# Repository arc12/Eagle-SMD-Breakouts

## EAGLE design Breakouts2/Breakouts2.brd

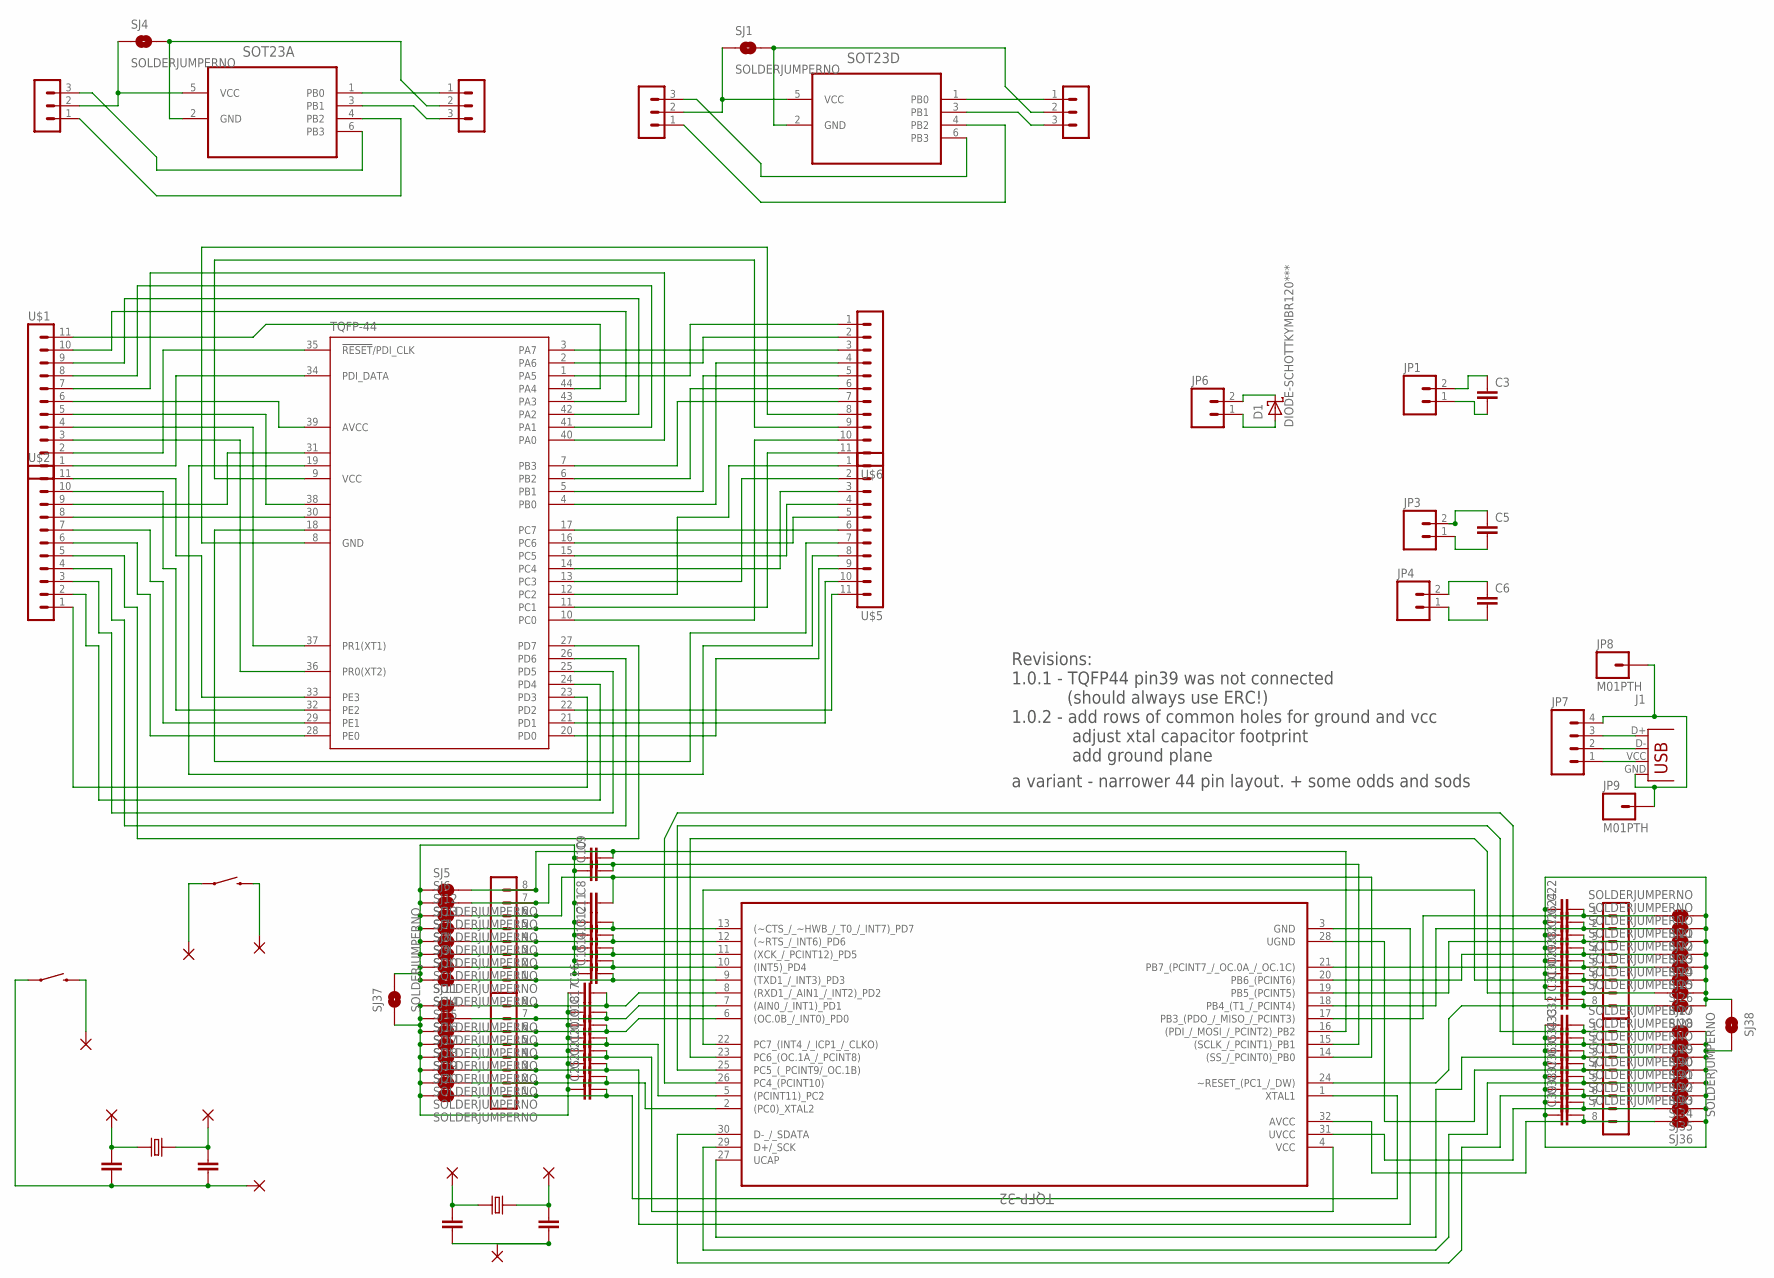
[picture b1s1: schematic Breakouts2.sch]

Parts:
C1, C2, C40, C41: C-EU025-024X044**100NF+22PF; C025-024X044
C3, C5, C6, C8, C9, C10, C11, C12, C13, C14, C15, C16, C17, C18, C19, C20, C21, C22, C23, C24, C25, C26, C27, C28, C29, C30, C31, C32, C33, C34, C35, C36, C37, C38, C39: C-EU1206; 1206
D1: DIODE-SCHOTTKYMBR120***; SOD123
J1: USB-FCI_SMD***; FCI_USB_B_SMD
JP1, JP3, JP4, JP6: M02PTH; 1X02
JP7: M04PTH; 1X04
JP8, JP9: M01PTH; 1X01
PAD1, PAD2, PAD3, PAD4, PAD5, PAD6, PAD7, PAD8, PAD9: WIREPAD1,6/0,8; 1,6/0,8
S1, S2: SWITCH-MOMENTARY-2PTH; TACTILE-PTH
SJ1, SJ4, SJ5, SJ6, SJ7, SJ8, SJ9, SJ10, SJ11, SJ12, SJ13, SJ14, SJ15, SJ16, SJ17, SJ18, SJ19, SJ20, SJ21, SJ22, SJ23, SJ24, SJ25, SJ26, SJ27, SJ28, SJ29, SJ30, SJ31, SJ32, SJ33, SJ34, SJ35, SJ36, SJ37, SJ38: SOLDERJUMPERNO; SJ_2S-NO
SOT23A, SOT23D: ATTINY10-TSHR; SOT95P280X145-6N
SV4, SV8, SV16, SV18: MA08-1
SV12, SV13, SV14, SV15: MA03-1
TQFP-32: AT90USB162-16AU; QFP80P900X900X120-32N
TQFP-44: XMEGA16A4A; TQFP44
U$1, U$2, U$5, U$6: MA11-1; MA11-1S
X1, X2: CRYSTAL-HC49U-V**16MHZ; HC49U-V

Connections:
GND: C1.2, C2.2, PAD8.1, S1.1
GND1: PAD4.1, S2.1
unnamed: TQFP-44.1 (PA5), U$6.1
unnamed: TQFP-44.2 (PA6), U$6.2
unnamed: TQFP-44.3 (PA7), U$6.3
unnamed: TQFP-44.4 (PB0), U$6.4
unnamed: TQFP-44.5 (PB1), U$6.5
unnamed: TQFP-44.6 (PB2), U$6.6
unnamed: TQFP-44.7 (PB3), U$6.7
unnamed: TQFP-44.8 (GND), U$6.8
unnamed: TQFP-44.9 (VCC), U$6.9
unnamed: TQFP-44.12 (PC2), U$5.1
unnamed: TQFP-44.11 (PC1), U$6.11
unnamed: TQFP-44.10 (PC0), U$6.10
unnamed: TQFP-44.13 (PC3), U$5.2
unnamed: TQFP-44.14 (PC4), U$5.3
unnamed: TQFP-44.15 (PC5), U$5.4
unnamed: TQFP-44.16 (PC6), U$5.5
unnamed: TQFP-44.17 (PC7), U$5.6
unnamed: TQFP-44.18 (GND1), U$5.7
unnamed: TQFP-44.19 (VCC1), U$5.8
unnamed: TQFP-44.20 (PD0), U$5.9
unnamed: TQFP-44.21 (PD1), U$5.10
unnamed: TQFP-44.22 (PD2), U$5.11
unnamed: TQFP-44.23 (PD3), U$2.1
unnamed: TQFP-44.24 (PD4), U$2.2
unnamed: C8.1, C9.1, C10.1, C11.1, C12.1, C13.1, C14.1, C15.1, SJ5.1, SJ6.1, SJ7.1, SJ8.1, SJ9.1, SJ10.1, SJ12.1, SJ13.1, SJ37.2
unnamed: C24.2, SJ22.2, SV4.2, TQFP-32.18 (PB4_(T1_/_PCINT4))
unnamed: C22.1, C24.1, C26.1, C27.1, C28.1, C29.1, C30.1, C31.1, SJ21.1, SJ22.1, SJ23.1, SJ24.1, SJ25.1, SJ26.1, SJ27.1, SJ28.1, SJ38.1
unnamed: C32.1, C33.1, C34.1, C35.1, C36.1, C37.1, C38.1, C39.1, SJ29.1, SJ30.1, SJ31.1, SJ32.1, SJ33.1, SJ34.1, SJ35.1, SJ36.1, SJ38.2
unnamed: C26.2, SJ23.2, SV4.3, TQFP-32.19 (PB5_(PCINT5))
unnamed: C16.1, C17.1, C18.1, C19.1, C20.1, C21.1, C23.1, C25.1, SJ11.1, SJ14.1, SJ15.1, SJ16.1, SJ17.1, SJ18.1, SJ19.1, SJ20.1, SJ37.1
unnamed: C27.2, SJ24.2, SV4.4, TQFP-32.20 (PB6_(PCINT6))
unnamed: J1.GND, JP7.4, JP8.1, JP9.1
unnamed: TQFP-44.25 (PD5), U$2.3
unnamed: TQFP-44.26 (PD6), U$2.4
unnamed: TQFP-44.27 (PD7), U$2.5
unnamed: TQFP-44.28 (PE0), U$2.6
unnamed: TQFP-44.29 (PE1), U$2.7
unnamed: TQFP-44.30 (GND2), U$2.8
unnamed: TQFP-44.31 (VCC2), U$2.9
unnamed: TQFP-44.32 (PE2), U$2.10
unnamed: TQFP-44.33 (PE3), U$2.11
unnamed: TQFP-44.34 (PDI_DATA), U$1.1
unnamed: TQFP-44.35 (!RESET!/PDI_CLK), U$1.2
unnamed: TQFP-44.36 (PR0(XT2)), U$1.3
unnamed: TQFP-44.37 (PR1(XT1)), U$1.4
unnamed: C41.1, PAD2.1, X2.1
unnamed: C40.1, PAD5.1, X2.2
unnamed: J1.D+, JP7.3
unnamed: J1.D-, JP7.2
unnamed: J1.VCC (VBUS), JP7.1
unnamed: PAD3.1, S2.3 (2)
unnamed: C3.1, JP1.2
unnamed: C3.2, JP1.1
unnamed: C5.1, JP3.2
unnamed: C5.2, JP3.1
unnamed: D1.K (C), JP6.2
unnamed: D1.A, JP6.1
unnamed: C6.1, JP4.2
unnamed: C6.2, JP4.1
unnamed: TQFP-44.38 (GND3), U$1.5
unnamed: TQFP-44.39 (AVCC), U$1.6
unnamed: TQFP-44.40 (PA0), U$1.7
unnamed: TQFP-44.41 (PA1), U$1.8
unnamed: TQFP-44.42 (PA2), U$1.9
unnamed: TQFP-44.43 (PA3), U$1.10
unnamed: TQFP-44.44 (PA4), U$1.11
unnamed: C23.2, SJ19.2, SV16.2, TQFP-32.2 ((PC0)_XTAL2)
unnamed: C25.2, SJ20.2, SV16.1, TQFP-32.1 (XTAL1)
unnamed: C19.2, SJ16.2, SV16.5, TQFP-32.5 ((PCINT11)_PC2)
unnamed: C18.2, SJ15.2, SV16.6, TQFP-32.6 ((OC.0B_/_INT0)_PD0)
unnamed: C17.2, SJ14.2, SV16.7, TQFP-32.7 ((AIN0_/_INT1)_PD1)
unnamed: C16.2, SJ11.2, SV16.8, TQFP-32.8 ((RXD1_/_AIN1_/_INT2)_PD2)
unnamed: C15.2, SJ10.2, SV18.1, TQFP-32.9 ((TXD1_/_INT3)_PD3)
unnamed: C14.2, SJ9.2, SV18.2, TQFP-32.10 ((INT5)_PD4)
unnamed: C13.2, SJ8.2, SV18.3, TQFP-32.11 ((XCK_/_PCINT12)_PD5)
unnamed: C12.2, SJ7.2, SV18.4, TQFP-32.12 ((~RTS_/_INT6)_PD6)
unnamed: C11.2, SJ13.2, SV18.5, TQFP-32.13 ((~CTS_/_~HWB_/_T0_/_INT7)_PD7)
unnamed: C20.2, SJ17.2, SV16.4, TQFP-32.4 (VCC)
unnamed: C21.2, SJ18.2, SV16.3, TQFP-32.3 (GND)
unnamed: C9.2, SJ5.2, SV18.8, TQFP-32.16 ((PDI_/_MOSI_/_PCINT2)_PB2)
unnamed: C10.2, SJ6.2, SV18.7, TQFP-32.15 ((SCLK_/_PCINT1)_PB1)
unnamed: C8.2, SJ12.2, SV18.6, TQFP-32.14 ((SS_/_PCINT0)_PB0)
unnamed: C22.2, SJ21.2, SV4.1, TQFP-32.17 (PB3_(PDO_/_MISO_/_PCINT3))
unnamed: C28.2, SJ25.2, SV4.5, TQFP-32.21 (PB7_(PCINT7_/_OC.0A_/_OC.1C))
unnamed: C29.2, SJ26.2, SV4.6, TQFP-32.22 (PC7_(INT4_/_ICP1_/_CLKO))
unnamed: C30.2, SJ27.2, SV4.7, TQFP-32.23 (PC6_(OC.1A_/_PCINT8))
unnamed: C31.2, SJ28.2, SV4.8, TQFP-32.24 (~RESET_(PC1_/_DW))
unnamed: C32.2, SJ29.2, SV8.1, TQFP-32.25 (PC5_(_PCINT9/_OC.1B))
unnamed: C33.2, SJ30.2, SV8.2, TQFP-32.26 (PC4_(PCINT10))
unnamed: C34.2, SJ31.2, SV8.3, TQFP-32.27 (UCAP)
unnamed: C35.2, SJ32.2, SV8.4, TQFP-32.28 (UGND)
unnamed: C36.2, SJ33.2, SV8.5, TQFP-32.29 (D+/_SCK)
unnamed: C37.2, SJ34.2, SV8.6, TQFP-32.30 (D-_/_SDATA)
unnamed: C38.2, SJ35.2, SV8.7, TQFP-32.31 (UVCC)
unnamed: C39.2, SJ36.2, SV8.8, TQFP-32.32 (AVCC)
unnamed: SOT23D.1 (PB0), SV13.1
unnamed: SJ1.2, SOT23D.2 (GND), SV13.2
unnamed: SOT23D.3 (PB1), SV13.3
unnamed: SOT23D.4 (PB2), SV12.1
unnamed: SJ1.1, SOT23D.5 (VCC), SV12.2
unnamed: SOT23D.6 (PB3), SV12.3
unnamed: SOT23A.1 (PB0), SV15.1
unnamed: SJ4.2, SOT23A.2 (GND), SV15.2
unnamed: SOT23A.3 (PB1), SV15.3
unnamed: SOT23A.4 (PB2), SV14.1
unnamed: SJ4.1, SOT23A.5 (VCC), SV14.2
unnamed: SOT23A.6 (PB3), SV14.3
unnamed: PAD1.1, S1.3 (2)
unnamed: C2.1, PAD6.1, X1.1
unnamed: C1.1, PAD7.1, X1.2
XTAL_GND: C40.2, C41.2, PAD9.1

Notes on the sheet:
Revisions: 1.0.1 - TQFP44 pin39 was not connected (should always use ERC!) 1.0.2 - add rows of common holes for ground and vcc adjust xtal capacitor footprint add ground plane
a variant - narrower 44 pin layout. + some odds and sods

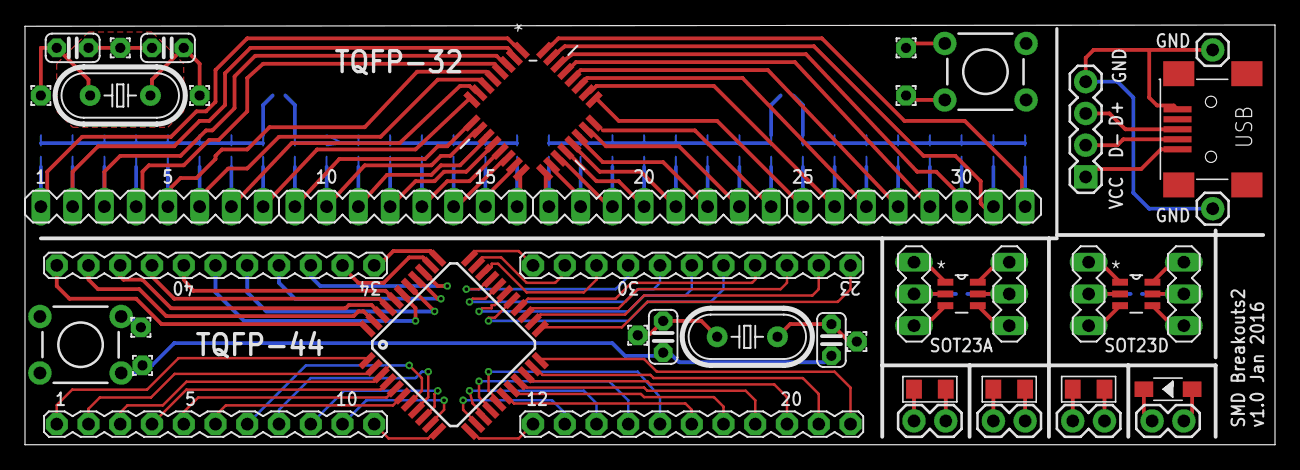
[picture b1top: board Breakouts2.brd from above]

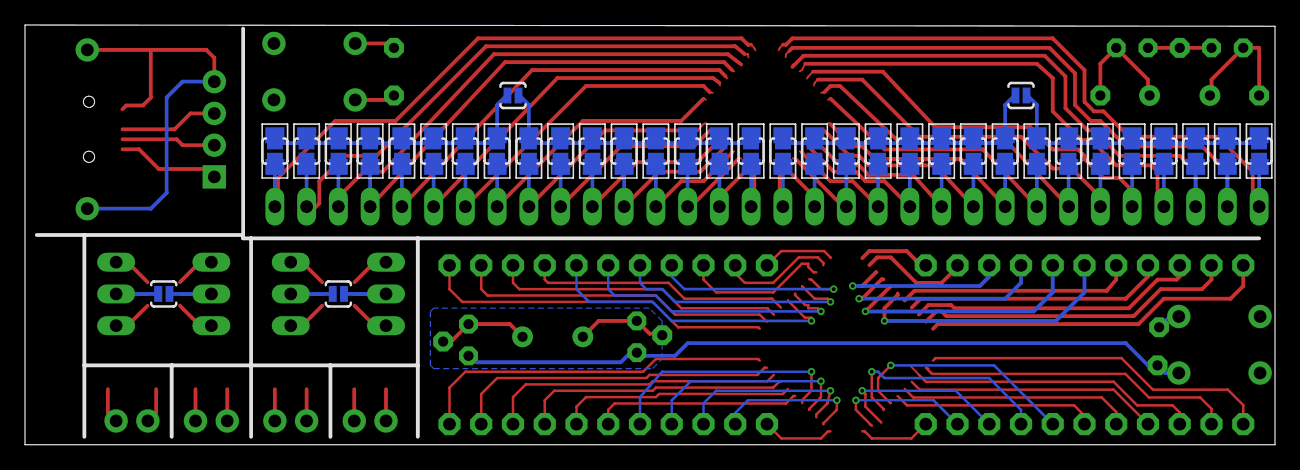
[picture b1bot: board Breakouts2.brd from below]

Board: 2 copper layers, 100.0 x 33.6 mm, 113 parts (68 on the bottom side), 113 nets.

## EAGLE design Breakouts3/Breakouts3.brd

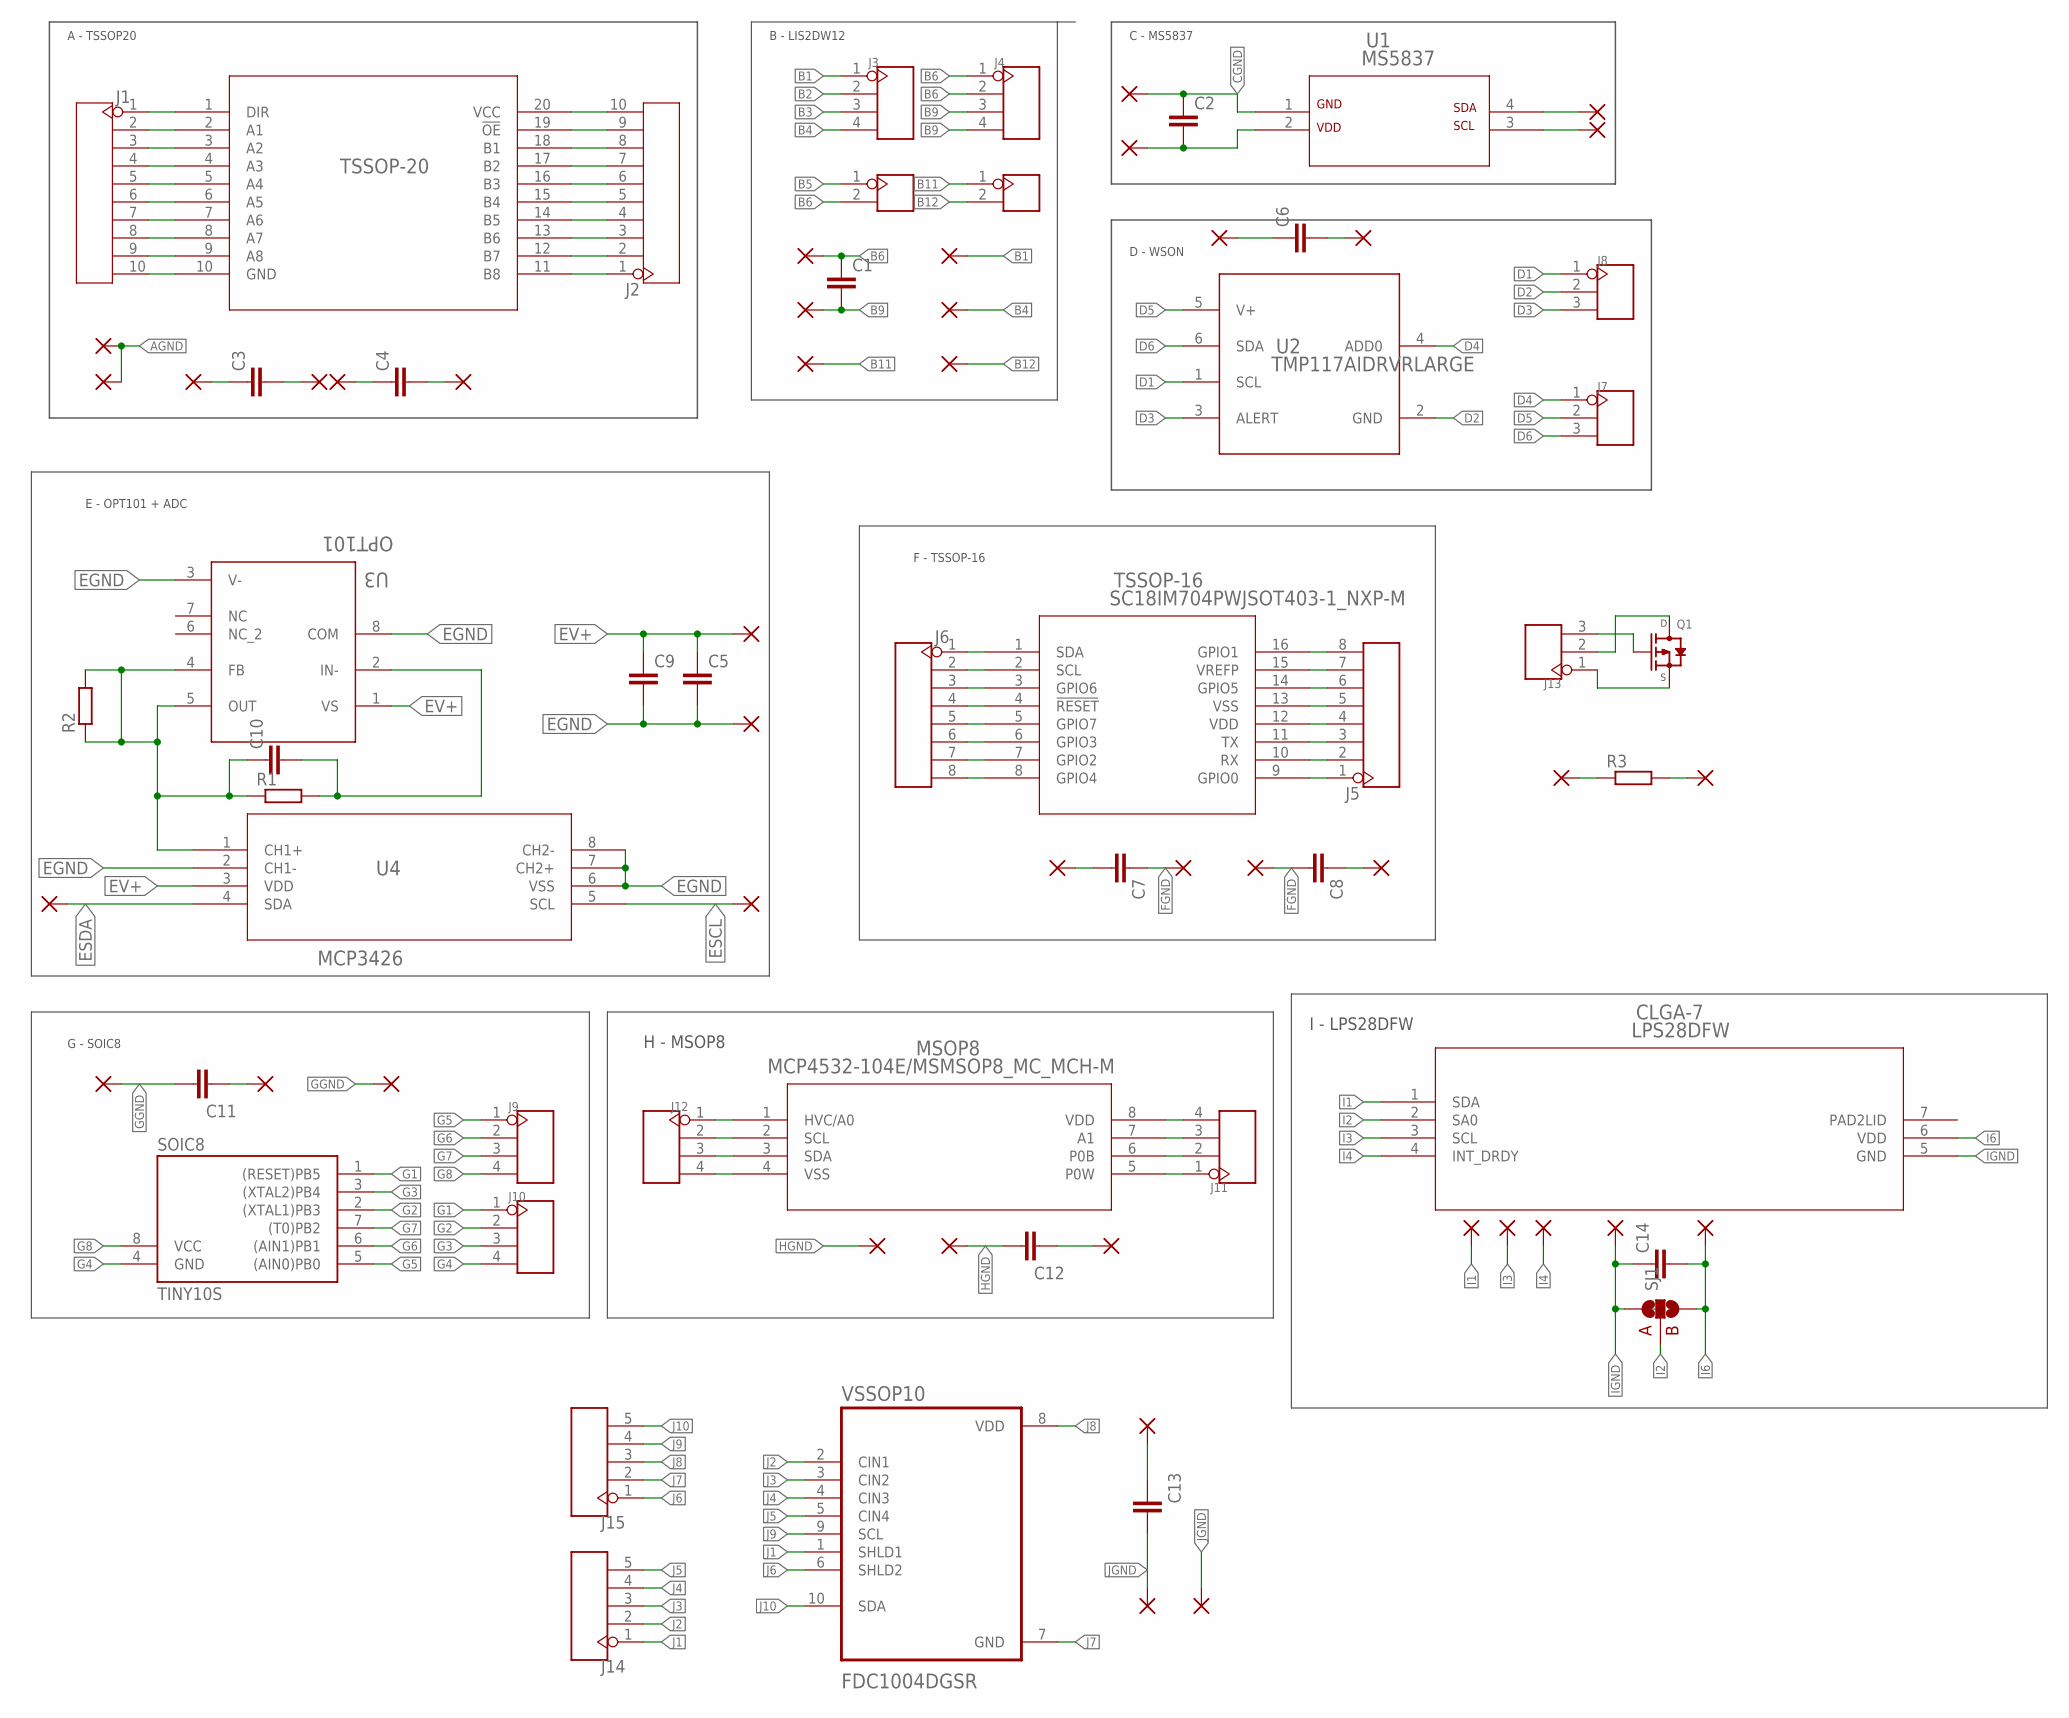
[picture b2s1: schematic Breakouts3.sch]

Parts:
C1, C2, C3, C4, C5, C6, C7, C8, C9, C10, C11, C12, C13, C14: C-EU1206; 1206
CLGA-7: LPS28DFW; CCLGA7_LPS28DFW_LARGE
J1, J2: HEADER-10P-2.54; 10P-2.54
J3, J4: HEADER-4P-SMD-1.27; 4P-1.27-SMD
J5, J6: HEADER-8P-2.54; 8P-2.54
J7, J8, J13: HEADER-3P-2.54; 3P-2.54
J9, J10, J11, J12: HEADER-4P-60/35MIL; 4P-65/35MIL
J14, J15: HEADER-5P-2.54; 5P-2.54
MSOP8: MCP4532-104E/MSMSOP8_MC_MCH-M; MSOP8_MC_MCH-M
PAD1, PAD2, PAD3, PAD4, PAD5, PAD6, PAD7, PAD8, PAD9, PAD10, PAD11, PAD12, PAD13, PAD14, PAD15, PAD16, PAD17, PAD18, PAD19, PAD20, PAD21, PAD22, PAD23, PAD24, PAD25, PAD26, PAD27, PAD28, PAD29, PAD30, PAD31, PAD32, PAD33, PAD34, PAD35, PAD36, PAD37, PAD38, PAD39, PAD40, PAD41, PAD42: WIREPADSMD1,27-254; SMD1,27-2,54
Q1: FDN338P_PMOSSOT23_LONG; SOT23_LONG
R1, R2, R3: R-EU_; 1206
SJ1: SOLDERJUMPER_2WAYT; SJ_2
SOIC8: TINY10S; SOIC8
TSSOP-16: SC18IM704PWJSOT403-1_NXP-M; SOT403-1_NXP-M
TSSOP-20: SN74ACT245PWRPW20-M; PW20-M
U1: MS5837; MS5837-02BA01_LARGE
U2: TMP117AIDRVRLARGE; DRV0006B-LARGE
U3: OPT101; DTL0008A_LARGE
U4: MCP3426; SOIC8-N_MC_MCH
U$1, U$2: HEADER-2P; 2P-1.27-SMD
VSSOP10: FDC1004DGSR; SOP50P490X110-10N

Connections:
AGND: PAD15.1, PAD16.1
B1: J3.1, PAD3.1
B2: J3.2
B3: J3.3
B4: J3.4, PAD6.1
B5: U$1.1
B6: C1.1, J4.1, J4.2, PAD1.1, U$1.2
B9: C1.2, J4.3, J4.4, PAD2.1
B11: PAD4.1, U$2.1
B12: PAD5.1, U$2.2
CGND: C2.1, PAD7.1, U1.1 (GND)
D1: J8.1, U2.1 (SCL)
D2: J8.2, U2.2 (GND)
D3: J8.3, U2.3 (ALERT)
D4: J7.1, U2.4 (ADD0)
D5: J7.2, U2.5 (V+)
D6: J7.3, U2.6 (SDA)
EGND: C5.2, C9.2, PAD24.1, U3.3 (V-), U3.8 (COM), U4.2 (CH1-), U4.6 (VSS), U4.7 (CH2+), U4.8 (CH2-)
ESCL: PAD25.1, U4.5 (SCL)
ESDA: PAD26.1, U4.4 (SDA)
EV+: C5.1, C9.1, PAD23.1, U3.1 (VS), U4.3 (VDD)
FGND: C7.1, C8.2, PAD20.1, PAD21.1
G1: J10.1, SOIC8.1 ((RESET)PB5)
G2: J10.2, SOIC8.2 ((XTAL1)PB3)
G3: J10.3, SOIC8.3 ((XTAL2)PB4)
G4: J10.4, SOIC8.4 (GND)
G5: J9.1, SOIC8.5 ((AIN0)PB0)
G6: J9.2, SOIC8.6 ((AIN1)PB1)
G7: J9.3, SOIC8.7 ((T0)PB2)
G8: J9.4, SOIC8.8 (VCC)
GGND: C11.1, PAD27.1, PAD29.1
HGND: C12.1, PAD31.1, PAD32.1
I1: CLGA-7.1 (SDA), PAD34.1
I2: CLGA-7.2 (SA0), SJ1.2
I3: CLGA-7.3 (SCL), PAD35.1
I4: CLGA-7.4 (INT_DRDY), PAD36.1
I6: C14.2, CLGA-7.6 (VDD), PAD38.1, SJ1.3
IGND: C14.1, CLGA-7.5 (GND), PAD37.1, SJ1.1
J1: J14.1, VSSOP10.1 (SHLD1)
J2: J14.2, VSSOP10.2 (CIN1)
J3: J14.3, VSSOP10.3 (CIN2)
J4: J14.4, VSSOP10.4 (CIN3)
J5: J14.5, VSSOP10.5 (CIN4)
J6: J15.1, VSSOP10.6 (SHLD2)
J7: J15.2, VSSOP10.7 (GND)
J8: J15.3, VSSOP10.8 (VDD)
J9: J15.4, VSSOP10.9 (SCL)
J10: J15.5, VSSOP10.10 (SDA)
JGND: C13.1, PAD41.1, PAD42.1
unnamed: J1.1, TSSOP-20.1 (DIR)
unnamed: C2.2, PAD8.1, U1.2 (VDD)
unnamed: PAD9.1, U1.4 (SDA)
unnamed: PAD10.1, U1.3 (SCL)
unnamed: J1.2, TSSOP-20.2 (A1)
unnamed: J1.3, TSSOP-20.3 (A2)
unnamed: J1.4, TSSOP-20.4 (A3)
unnamed: J1.5, TSSOP-20.5 (A4)
unnamed: J1.6, TSSOP-20.6 (A5)
unnamed: J1.7, TSSOP-20.7 (A6)
unnamed: J1.8, TSSOP-20.8 (A7)
unnamed: J1.9, TSSOP-20.9 (A8)
unnamed: J1.10, TSSOP-20.10 (GND)
unnamed: J2.10, TSSOP-20.20 (VCC)
unnamed: J2.9, TSSOP-20.19 (!OE)
unnamed: J2.8, TSSOP-20.18 (B1)
unnamed: J2.7, TSSOP-20.17 (B2)
unnamed: J2.6, TSSOP-20.16 (B3)
unnamed: J2.5, TSSOP-20.15 (B4)
unnamed: J2.4, TSSOP-20.14 (B5)
unnamed: J2.3, TSSOP-20.13 (B6)
unnamed: J2.2, TSSOP-20.12 (B7)
unnamed: J2.1, TSSOP-20.11 (B8)
unnamed: C3.1, PAD11.1
unnamed: C3.2, PAD13.1
unnamed: C4.1, PAD12.1
unnamed: C4.2, PAD14.1
unnamed: C6.1, PAD17.1
unnamed: C6.2, PAD18.1
unnamed: C7.2, PAD22.1
unnamed: PAD33.1, R3.1
unnamed: C10.1, R1.1, R2.1, R2.2, U3.4 (FB), U3.5 (OUT), U4.1 (CH1+)
unnamed: C8.1, PAD19.1
unnamed: J6.1, TSSOP-16.1 (SDA)
unnamed: J6.2, TSSOP-16.2 (SCL)
unnamed: J6.3, TSSOP-16.3 (GPIO6)
unnamed: J6.4, TSSOP-16.4 (!RESET)
unnamed: J6.5, TSSOP-16.5 (GPIO7)
unnamed: J6.6, TSSOP-16.6 (GPIO3)
unnamed: J6.7, TSSOP-16.7 (GPIO2)
unnamed: J6.8, TSSOP-16.8 (GPIO4)
unnamed: J5.8, TSSOP-16.16 (GPIO1)
unnamed: J5.7, TSSOP-16.15 (VREFP)
unnamed: J5.6, TSSOP-16.14 (GPIO5)
unnamed: J5.5, TSSOP-16.13 (VSS)
unnamed: J5.4, TSSOP-16.12 (VDD)
unnamed: J5.3, TSSOP-16.11 (TX)
unnamed: J5.2, TSSOP-16.10 (RX)
unnamed: J5.1, TSSOP-16.9 (GPIO0)
unnamed: C10.2, R1.2, U3.2 (IN-)
unnamed: C11.2, PAD28.1
unnamed: J12.1, MSOP8.1 (HVC/A0)
unnamed: J12.2, MSOP8.2 (SCL)
unnamed: J12.3, MSOP8.3 (SDA)
unnamed: J12.4, MSOP8.4 (VSS)
unnamed: J11.4, MSOP8.8 (VDD)
unnamed: J11.3, MSOP8.7 (A1)
unnamed: J11.2, MSOP8.6 (P0B)
unnamed: J11.1, MSOP8.5 (P0W)
unnamed: PAD39.1, R3.2
unnamed: C12.2, PAD30.1
unnamed: J13.3, Q1.1 (G)
unnamed: J13.2, Q1.3 (D)
unnamed: J13.1, Q1.2 (S)
unnamed: C13.2, PAD40.1

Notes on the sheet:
B - LIS2DW12
A - TSSOP20
C - MS5837
D - WSON
E - OPT101 + ADC
F - TSSOP-16
G - SOIC8
H - MSOP8
I - LPS28DFW

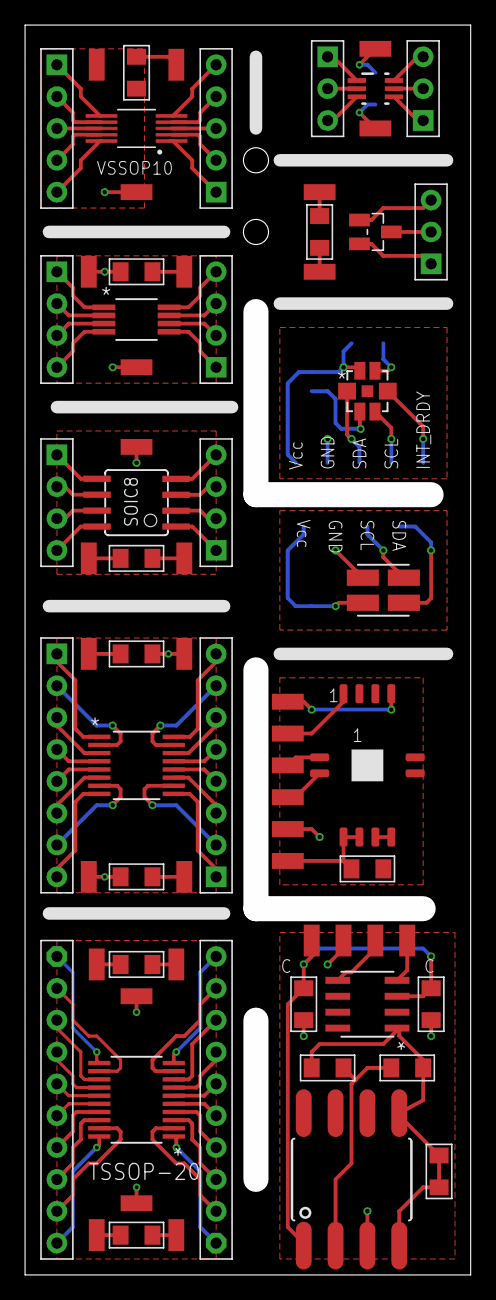
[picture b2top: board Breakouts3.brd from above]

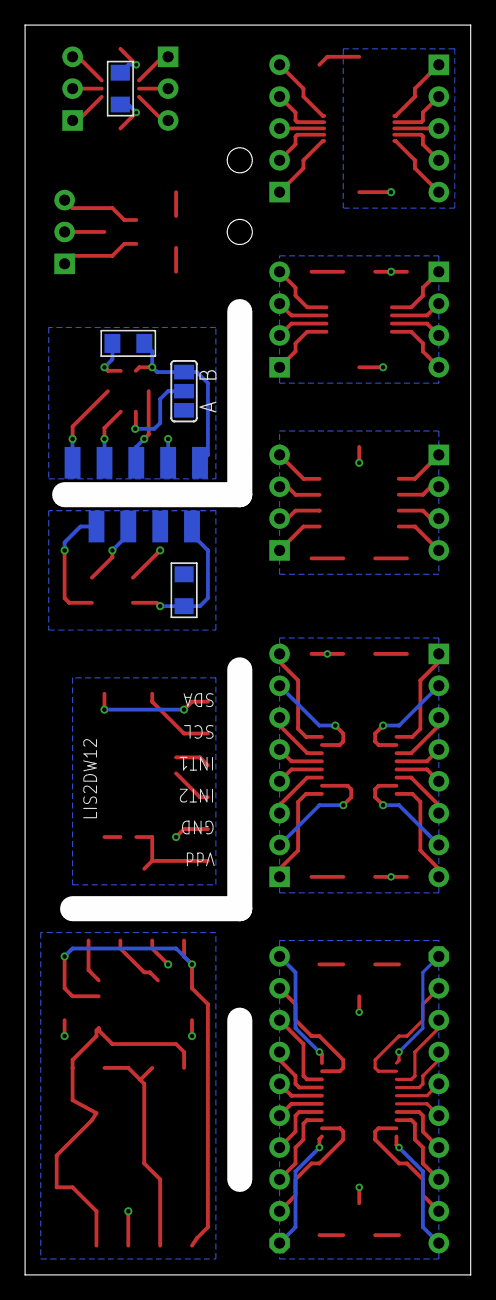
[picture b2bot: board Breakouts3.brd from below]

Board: 2 copper layers, 33.5 x 97.7 mm, 88 parts (13 on the bottom side), 111 nets.

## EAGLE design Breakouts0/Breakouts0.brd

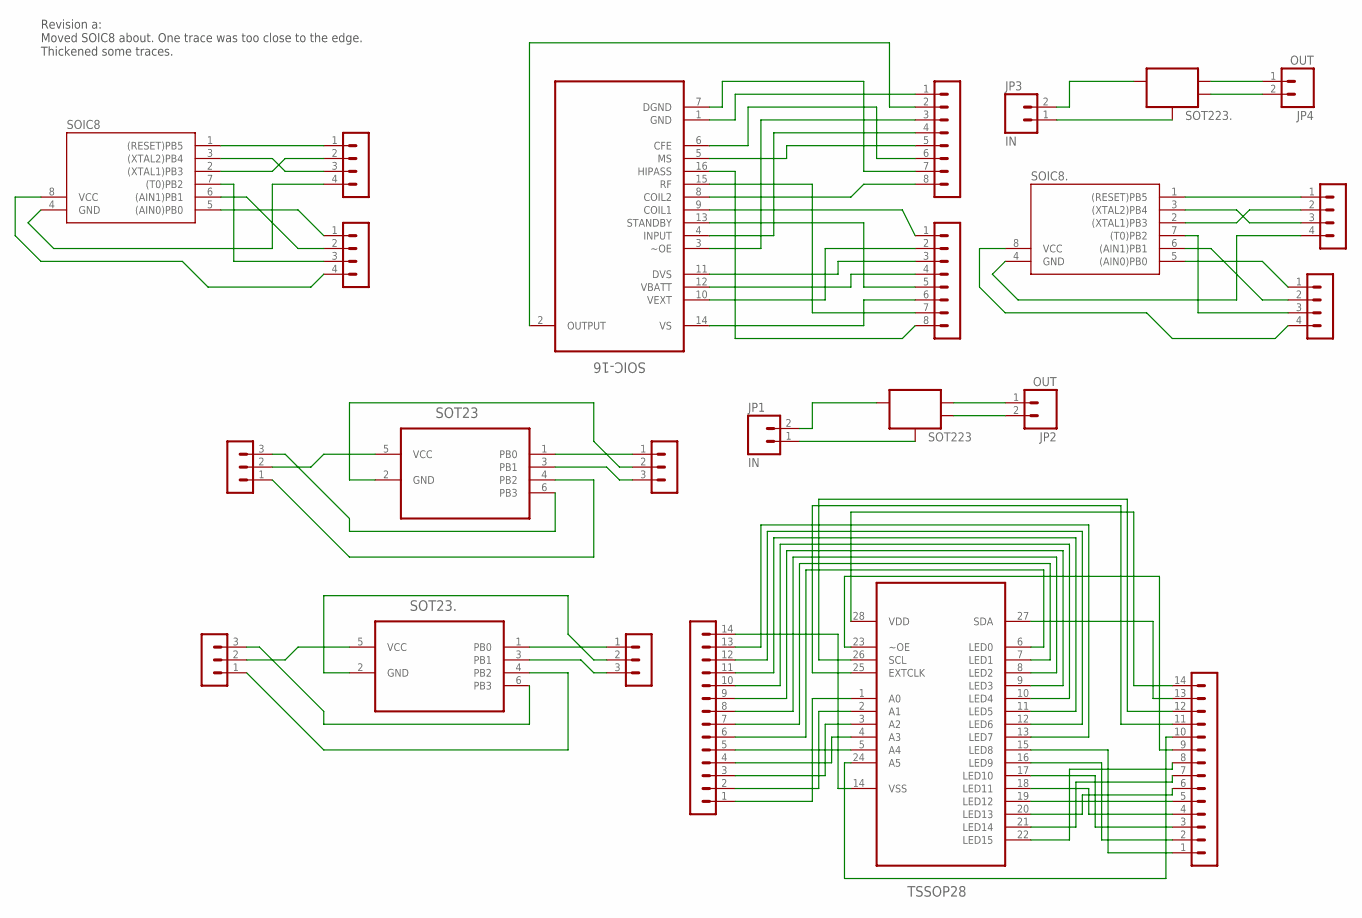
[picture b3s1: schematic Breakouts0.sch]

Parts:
JP1, JP3: IN; 1X02
JP2, JP4: OUT; 1X02
SOIC8, SOIC8.: TINY10S; SOIC8
SOIC-16: U2270B-MFPY; SOIC127P600X140-16N
SOT23, SOT23.: ATTINY10-TSHR; SOT95P280X145-6N
SOT223, SOT223.: SOT223SOT223; SOT223
SV1, SV2: MA08-1
SV3, SV4, SV21, SV22: MA03-1
SV5, SV9: MA14-1
SV8, SV10, SV13, SV14: MA04-1
TSSOP28: PCA9685PW; SOP65P640X110-28N

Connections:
unnamed: SOT23..1 (PB0), SV4.1
unnamed: SOT23..2 (GND), SV4.2
unnamed: SOT23..3 (PB1), SV4.3
unnamed: SOT23..4 (PB2), SV3.1
unnamed: SOT23..5 (VCC), SV3.2
unnamed: SOT23..6 (PB3), SV3.3
unnamed: JP3.2, SOT223..3 (IN)
unnamed: JP3.1, SOT223..1 (ADJ)
unnamed: JP4.1, SOT223..2 (OUT)
unnamed: JP4.2, SOT223..4 (OUT)
unnamed: SOIC8..1 ((RESET)PB5), SV8.1
unnamed: SOIC8..2 ((XTAL1)PB3), SV8.2
unnamed: SOIC8..3 ((XTAL2)PB4), SV8.3
unnamed: SOIC8..4 (GND), SV8.4
unnamed: SOIC8..5 ((AIN0)PB0), SV10.1
unnamed: SOIC8..6 ((AIN1)PB1), SV10.2
unnamed: SOIC8..7 ((T0)PB2), SV10.3
unnamed: SOIC8..8 (VCC), SV10.4
unnamed: SOIC8.1 ((RESET)PB5), SV13.1
unnamed: SOIC8.2 ((XTAL1)PB3), SV13.2
unnamed: SOIC8.3 ((XTAL2)PB4), SV13.3
unnamed: SOIC8.4 (GND), SV13.4
unnamed: SOIC8.5 ((AIN0)PB0), SV14.1
unnamed: SOIC8.6 ((AIN1)PB1), SV14.2
unnamed: SOIC8.7 ((T0)PB2), SV14.3
unnamed: SOIC8.8 (VCC), SV14.4
unnamed: SOIC-16.1 (GND), SV1.1
unnamed: SOIC-16.2 (OUTPUT), SV1.2
unnamed: SOIC-16.3 (~OE), SV1.3
unnamed: SOIC-16.4 (INPUT), SV1.4
unnamed: SOIC-16.5 (MS), SV1.5
unnamed: SOIC-16.6 (CFE), SV1.6
unnamed: SOIC-16.7 (DGND), SV1.7
unnamed: SOIC-16.8 (COIL2), SV1.8
unnamed: SOIC-16.9 (COIL1), SV2.1
unnamed: SOIC-16.10 (VEXT), SV2.2
unnamed: SOIC-16.11 (DVS), SV2.3
unnamed: SOIC-16.12 (VBATT), SV2.4
unnamed: SOIC-16.13 (STANDBY), SV2.5
unnamed: SOIC-16.14 (VS), SV2.6
unnamed: SOIC-16.15 (RF), SV2.7
unnamed: SOIC-16.16 (HIPASS), SV2.8
unnamed: SOT23.1 (PB0), SV22.1
unnamed: SOT23.2 (GND), SV22.2
unnamed: SOT23.3 (PB1), SV22.3
unnamed: SOT23.4 (PB2), SV21.1
unnamed: SOT23.5 (VCC), SV21.2
unnamed: SOT23.6 (PB3), SV21.3
unnamed: JP1.2, SOT223.3 (IN)
unnamed: JP2.1, SOT223.2 (OUT)
unnamed: JP2.2, SOT223.4 (OUT)
unnamed: SV5.1, TSSOP28.1 (A0)
unnamed: SV5.14, TSSOP28.14 (VSS)
unnamed: SV9.1, TSSOP28.15 (LED8)
unnamed: SV9.14, TSSOP28.28 (VDD)
unnamed: SV5.2, TSSOP28.2 (A1)
unnamed: SV5.3, TSSOP28.3 (A2)
unnamed: SV5.4, TSSOP28.4 (A3)
unnamed: SV5.5, TSSOP28.5 (A4)
unnamed: SV5.6, TSSOP28.6 (LED0)
unnamed: SV5.7, TSSOP28.7 (LED1)
unnamed: SV5.8, TSSOP28.8 (LED2)
unnamed: SV5.9, TSSOP28.9 (LED3)
unnamed: SV5.10, TSSOP28.10 (LED4)
unnamed: SV5.11, TSSOP28.11 (LED5)
unnamed: SV5.12, TSSOP28.12 (LED6)
unnamed: SV5.13, TSSOP28.13 (LED7)
unnamed: SV9.2, TSSOP28.16 (LED9)
unnamed: SV9.3, TSSOP28.17 (LED10)
unnamed: SV9.4, TSSOP28.18 (LED11)
unnamed: SV9.5, TSSOP28.19 (LED12)
unnamed: SV9.6, TSSOP28.20 (LED13)
unnamed: SV9.7, TSSOP28.21 (LED14)
unnamed: SV9.8, TSSOP28.22 (LED15)
unnamed: SV9.10, TSSOP28.24 (A5)
unnamed: SV9.9, TSSOP28.23 (~OE)
unnamed: SV9.11, TSSOP28.25 (EXTCLK)
unnamed: SV9.12, TSSOP28.26 (SCL)
unnamed: SV9.13, TSSOP28.27 (SDA)
unnamed: JP1.1, SOT223.1 (ADJ)

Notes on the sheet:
Revision a: Moved SOIC8 about. One trace was too close to the edge. Thickened some traces.

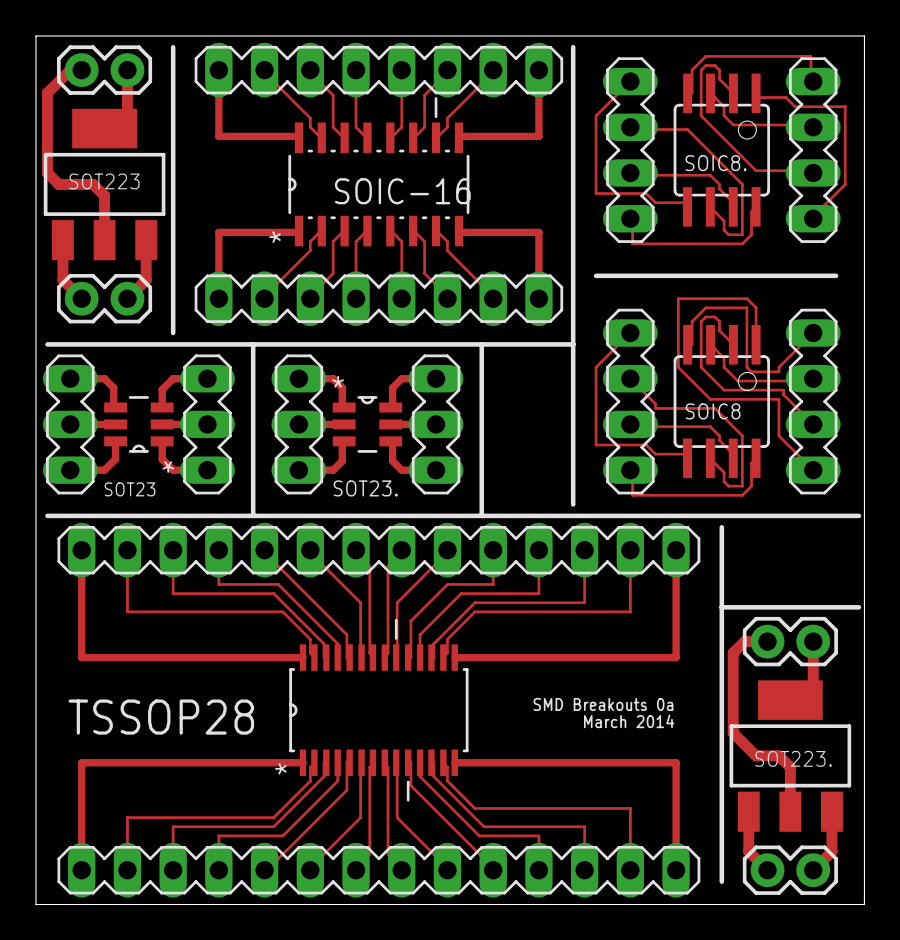
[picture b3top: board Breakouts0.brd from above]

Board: 2 copper layers, 46.0 x 48.2 mm, 24 parts (0 on the bottom side), 80 nets.

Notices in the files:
parts and their libraries:
SparkFun-Connectors: Licensing: CC v3.0 Share-Alike You are welcome to use this library for commercial purposes.
COPYRIGHT: Copyright (C) 2025 Ultra Librarian. All rights reserved.
